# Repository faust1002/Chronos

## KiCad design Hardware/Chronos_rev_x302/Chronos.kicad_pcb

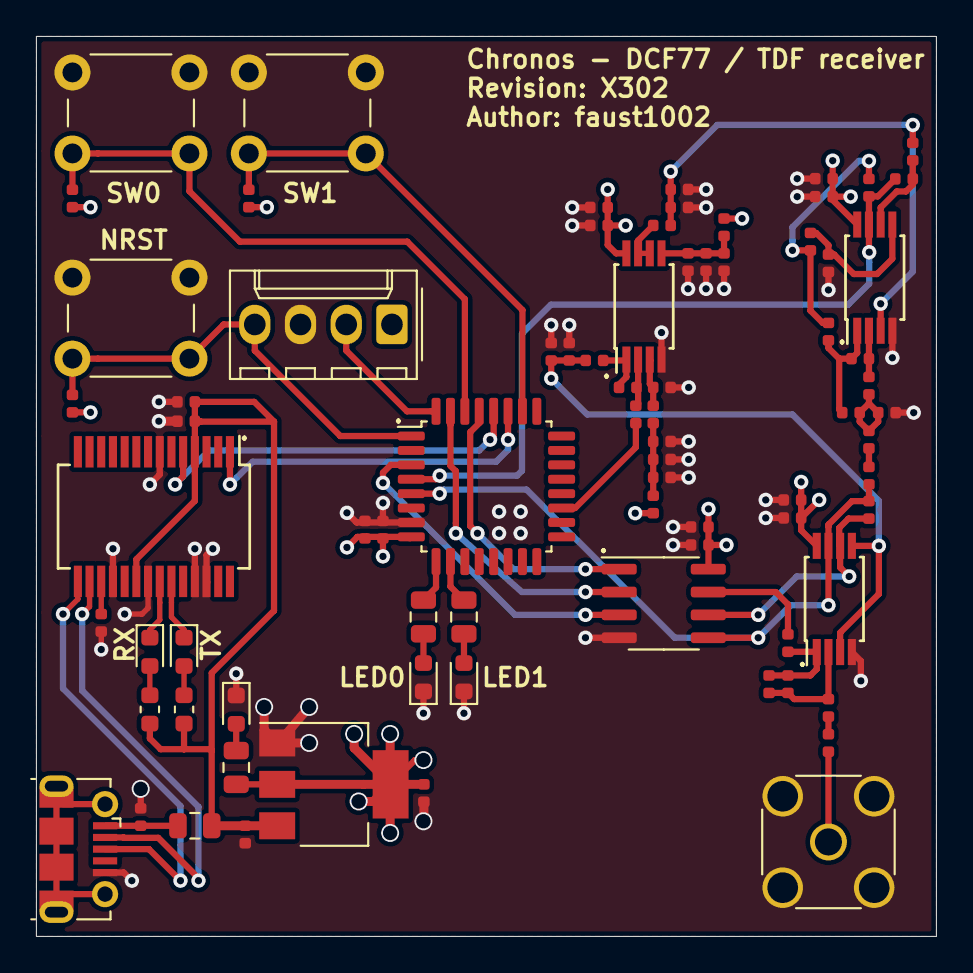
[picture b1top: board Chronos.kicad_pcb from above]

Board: 4 copper layers, 50.0 x 50.0 mm, 79 parts (0 on the bottom side), 49 nets.

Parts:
C1, C11, C13, C17: 10nF; C_0402_1005Metric
C2, C6, C7, C9, C14, C18, C24, C26, C29, C30, C33: 100nF; C_0402_1005Metric
C3, C8, C10, C15, C19, C25: 4.7uF; C_0402_1005Metric
C4, C5, C27, C28, C31, C32: 10uF; C_0402_1005Metric
C12, C16: 56pF; C_0402_1005Metric
C20: 4.7nF; C_0402_1005Metric
C21, C22, C23: 100pF; C_0402_1005Metric
D1, D2, D3, D4, D5: LED; LED_0603_1608Metric
FB1: Ferrite_Bead; L_0805_2012Metric
J1: USB_B_Micro; USB_Micro-B_Molex-105017-0001
J2: Conn_01x04; Molex_KK-254_AE-6410-04A_1x04_P2.54mm_Vertical
J3: Input; SMA_Amphenol_132134_Vertical
R1, R5, R6: 56; R_0805_2012Metric
R2, R3: 270; R_0603_1608Metric
R4, R7, R8, R9: 1k; R_0402_1005Metric
R10, R15: 33k; R_0402_1005Metric
R11: 680; R_0402_1005Metric
R12, R16: 6.8k; R_0402_1005Metric
R13, R17: 470; R_0402_1005Metric
R14: 1.5k; R_0402_1005Metric
R18, R19, R20, R21, R22, R23, R25, R26: 20k; R_0402_1005Metric
R24, R27: 100; R_0402_1005Metric
SW1, SW2, SW3: SW_Push; SW_PUSH_6mm
U1: STM8L151K6T6; LQFP-32_7x7mm_P0.8mm
U2: AMS1117-3.3; SOT-223-3_TabPin2
U3: FT232RL; SSOP-28_5.3x10.2mm_P0.65mm
U4, U6, U7: TS462CPT; TSSOP-8_4.4x3mm_P0.65mm
U5: MCP41010; SOIC-8_3.9x4.9mm_P1.27mm

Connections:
+3V3: C5.1, C7.1, C8.1, C9.1, C10.1, C14.1, C15.1, C18.1, C19.1, C24.1, C25.1, J2.1, R1.1, R4.1, R7.2, R8.2, R18.1, R25.1, U1.8, U2.2, U4.8, U5.8, U6.8, U7.8
+5V: C2.1, C3.1, C4.1, FB1.1, R2.1, R3.1, U2.3, U3.4, U3.20
/ADC0: C23.1, R16.1, U1.4, U6.7
/ADC1: C16.1, C17.2, U1.5, U4.7, U5.5
/D+: J1.3, U3.15
/D-: J1.2, U3.16
/DAC: R20.2, U1.19
/LED0: R5.1, U1.9
/LED1: R6.1, U1.10
/MOSI: U1.3, U5.3
/NRST: J2.4, R4.2, SW1.2, U1.1
/NSS: U1.29, U5.1
/REF: C28.1, C29.1, R17.2, R27.1, U6.3
/RXD: U1.28, U3.5
/SCK: U1.31, U5.2
/SW0: R7.1, SW2.2, U1.30
/SW1: R8.1, SW3.2, U1.26
/SWIM: J2.2, U1.32
/TXD: U1.27, U3.1
/Vbias: C32.1, C33.1, R24.1, U4.3, U4.5
GND: C1.2, C2.2, C3.2, C4.2, C5.2, C6.2, C7.2, C8.2, C9.2, C10.2, C14.2, C15.2, C18.2, C19.2, C20.2, C22.2, C24.2, C25.2, C26.2, C27.2, C28.2, C29.2, C30.2, C31.2, C32.2, C33.2, D1.1, D4.1, D5.1, J1.5, J2.3, J3.2, R19.2, R22.2, R26.2, SW1.1, SW2.1, SW3.1, U1.7, U2.1, U3.7, U3.18, U3.21, U3.25, U3.26, U4.4, U5.4, U6.4, U7.4
unnamed: C1.1, FB1.2, J1.1
unnamed: C6.1, U3.17
unnamed: C11.1, J3.1
unnamed: C11.2, R9.1
unnamed: C12.1, C13.2, R10.2, U4.1
unnamed: C12.2, R9.2, R10.1, U4.2
unnamed: C13.1, U5.7
unnamed: C16.2, U4.6, U5.6
unnamed: C17.1, R11.2
unnamed: C20.1, R11.1, R12.2, R13.2
unnamed: C21.1, R12.1, R14.2, U6.1
unnamed: C21.2, R13.1, U6.2
unnamed: C22.1, R15.1, U6.5
unnamed: C23.2, R14.1, R15.2
unnamed: C26.1, C27.1, R25.2, R26.1, U7.5
unnamed: C30.1, C31.1, R18.2, R19.1, R21.2
unnamed: D1.2, R1.2
unnamed: D2.1, U3.23
unnamed: D2.2, R2.2
unnamed: D3.1, U3.22
unnamed: D3.2, R3.2
unnamed: D4.2, R5.2
unnamed: D5.2, R6.2
unnamed: R16.2, R17.1, U6.6
unnamed: R20.1, R23.2, U7.2
unnamed: R21.1, R22.1, U7.3
unnamed: R23.1, R24.2, U7.1
unnamed: R27.2, U7.6, U7.7

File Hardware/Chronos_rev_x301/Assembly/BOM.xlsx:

Designator | Value | Footprint | LSCS part# | Comment
C1, C11, C13, C17 | 10nF | Capacitor_SMD:C_0402_1005Metric | C15195 | N/A
C2, C6, C7, C8, C9, C14, C18, C24, C26, C29, C30, C33 | 100nF | Capacitor_SMD:C_0402_1005Metric | C1525 | N/A
C3, C10, C15, C19, C25 | 4.7uF | Capacitor_SMD:C_0402_1005Metric | C23733 | N/A
C4, C5, C27, C28, C31, C32 | 10uF | Capacitor_SMD:C_0402_1005Metric | C15525 | N/A
C12, C16 | 56pF | Capacitor_SMD:C_0402_1005Metric | C1572 | N/A
C20 | 4.7nF | Capacitor_SMD:C_0402_1005Metric | C1538 | N/A
C21, C22, C23 | 100pF | Capacitor_SMD:C_0402_1005Metric | C1546 | N/A
D1, D2, D3, D4, D5 | LED | LED_SMD:LED_0603_1608Metric | C72043 | N/A
FB1 | Ferrite bead | Inductor_SMD:L_0805_2012Metric | C1017 | N/A
J1 | N/A | Connector_USB:USB_Micro-B_Molex-105017-0001 | N/A | Do not populate
J2 | N/A | Connector_Molex:Molex_KK-254_AE-6410-04A_1x04_P2.54mm_Vertical | N/A | Do not populate
J3 | N/A | Connector_Coaxial:SMA_Amphenol_132134_Vertical | N/A | Do not populate
R1, R5, R6 | 56 | Resistor_SMD:R_0805_2012Metric | C17757 | N/A
R2, R3 | 270 | Resistor_SMD:R_0603_1608Metric | C22966 | N/A
R4, R7, R8, R9 | 1k | Resistor_SMD:R_0402_1005Metric | C11702 | N/A
R10, R15 | 33k | Resistor_SMD:R_0402_1005Metric | C25779 | N/A
R11 | 680 | Resistor_SMD:R_0402_1005Metric | C25130 | N/A
R12, R16 | 6.8k | Resistor_SMD:R_0402_1005Metric | C25917 | N/A
R13, R17 | 470 | Resistor_SMD:R_0402_1005Metric | C25117 | N/A
R14 | 1.5k | Resistor_SMD:R_0402_1005Metric | C25867 | N/A
R18, R19, R20, R21, R22, R23, R25, R26 | 20k | Resistor_SMD:R_0402_1005Metric | C25765 | N/A
R24, R27 | 100 | Resistor_SMD:R_0402_1005Metric | C25076 | N/A
SW1, SW2, SW3 | N/A | Button_Switch_THT:SW_PUSH_6mm | N/A | Do not populate
U1 | STM8L151K6T6 | Package_QFP:LQFP-32_7x7mm_P0.8mm | C8259 | N/A
U2 | AMS1117-3.3 | Package_TO_SOT_SMD:SOT-223-3_TabPin2 | C6186 | N/A
U3 | FT232RL | Package_SO:SSOP-28_5.3x10.2mm_P0.65mm | C8690 | N/A
U4, U6, U7 | TS462CPT | Package_SO:TSSOP-8_4.4x3mm_P0.65mm | C155576 | N/A
U5 | MCP41010 | Package_SO:SOIC-8_3.9x4.9mm_P1.27mm | C17064 | N/A

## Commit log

2020-05-24 Initial version of a test software
2020-06-01 Reference model - initial commit
2020-06-01 Add hardware related files
2020-06-01 Reference model - Switch from numpy to scipy
2020-06-01 Reference modem - add 60kHz tone
2020-06-01 Reference model - reformat plots
2020-06-01 Reference model - filtering (extremely rough sketch)
2020-06-03 Reference model - refactor the initial sketch
2020-06-03 Reference modem - replace dummy print function with a proper logging
2020-06-03 Reference modem - extract carrier frequency and sampling frequency as (global) variables
2020-06-04 Reference model - add encode bitstream function
2020-06-06 Reference model - update shebang
2020-06-08 Reference model - switch to complex waveforms instead of real ones (to implement phase modulation easily)
2020-06-08 Reference model - remove Qt5 backend
2020-06-08 Hardware - upload DCF77 specification provided by PTB
2020-06-09 Reference modem - instead of using real part of a complex waveform and then shifting it by -pi / 2 simply use an imaginary part
2020-06-15 Reference model - add PRSK sequence generation
2020-06-17 Reference model - refactor signal generator flow
2020-06-17 Reference model - add phase modulation
2020-06-27 Reference model - add Hilbert transform to demodulate a test vector (initial draft)
